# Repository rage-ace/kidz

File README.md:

# kidz

Find out more at [notes.skytect.one/robocup](https://notes.skytect.one/robocup)!

```bash
.
├── designs/               # All CAD designs are located here
│   └── pcb-schematics/        # PCB schematics
│       ├── layer1/                # Layer 1 PCB
│       ├── layer2/                # Layer 2 PCB
│       ├── layer3/                # Layer 3 PCB
│       └── layer4/                # Layer 4 PCB
├── software/              # All code is located here
│   ├── coral/             # Code for the Coral Dev Board Mini
│   │   └── ...
│   └── microcontrollers/  # Code for the Teensy 4.0 and STM32F103CBT6s
│       ├── include/           # Shared header files
│       ├── lib/               # Shared libraries
│       ├── src/
│       │   ├── stm32_mux/         # Code for the Layer 1 STM32
│       │   │   ├── include/           # Header files
│       │   │   ├── lib/               # Libraries
│       │   │   ├── main.cpp           # Source code
│       │   │   └── ...
│       │   ├── stm32_imu/         # Code for the Layer 4 IMU STM32
│       │   │   ├── include/           # Header files
│       │   │   ├── lib/               # Libraries
│       │   │   ├── main.cpp           # Source code
│       │   │   └── ...
│       │   ├── stm32_tof/        # Code for the Layer 4 TOF STM32
│       │   │   ├── include/           # Header files
│       │   │   ├── lib/               # Libraries
│       │   │   ├── main.cpp           # Source code
│       │   │   └── ...
│       │   ├── teensy/            # Code for the Layer 3 Teensy
│       │   │   ├── include/           # Header files
│       │   │   ├── lib/               # Libraries
│       │   │   ├── main.cpp           # Source code
│       │   │   └── ...
│       │   └── ...            # Shared source code
│       ├── platform.ini       # PlatformIO configuration file
│       └── ...
├── .gitignore
├── LICENSE
└── README.md
```

## Coral

[Click Me!](software/coral)

## Microcontrollers

### Execution

```bash
cd software/microcontrollers
# Upload and run to Teensy
pio run -e teensy -t upload -t monitor
# Upload to Layer 1 STM32
pio run -e stm32_mux -t upload
```

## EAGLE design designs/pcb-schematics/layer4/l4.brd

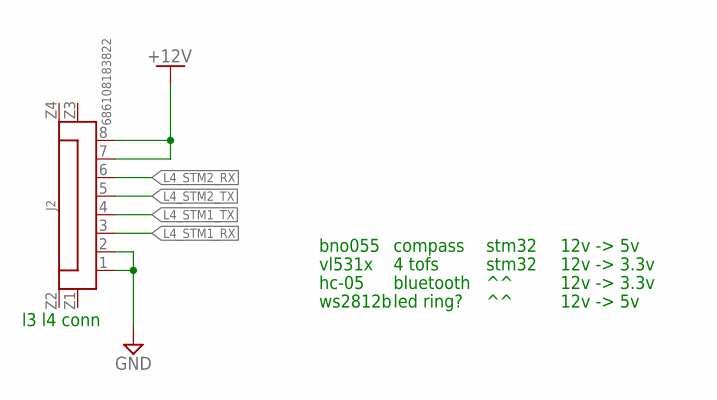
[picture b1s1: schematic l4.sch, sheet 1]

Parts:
J2: 686108183822

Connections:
+12V: J2.7, J2.8; also elsewhere on the board
GND: J2.1, J2.2; also elsewhere on the board
L4_STM1_RX: J2.3; also elsewhere on the board
L4_STM1_TX: J2.4; also elsewhere on the board
L4_STM2_RX: J2.6; also elsewhere on the board
L4_STM2_TX: J2.5; also elsewhere on the board

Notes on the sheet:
compass
stm32
4 tofs
bluetooth
led ring?
bno055
ws2812b
vl531x
hc-05
12v -> 5v
12v -> 3.3v
l3 l4 conn

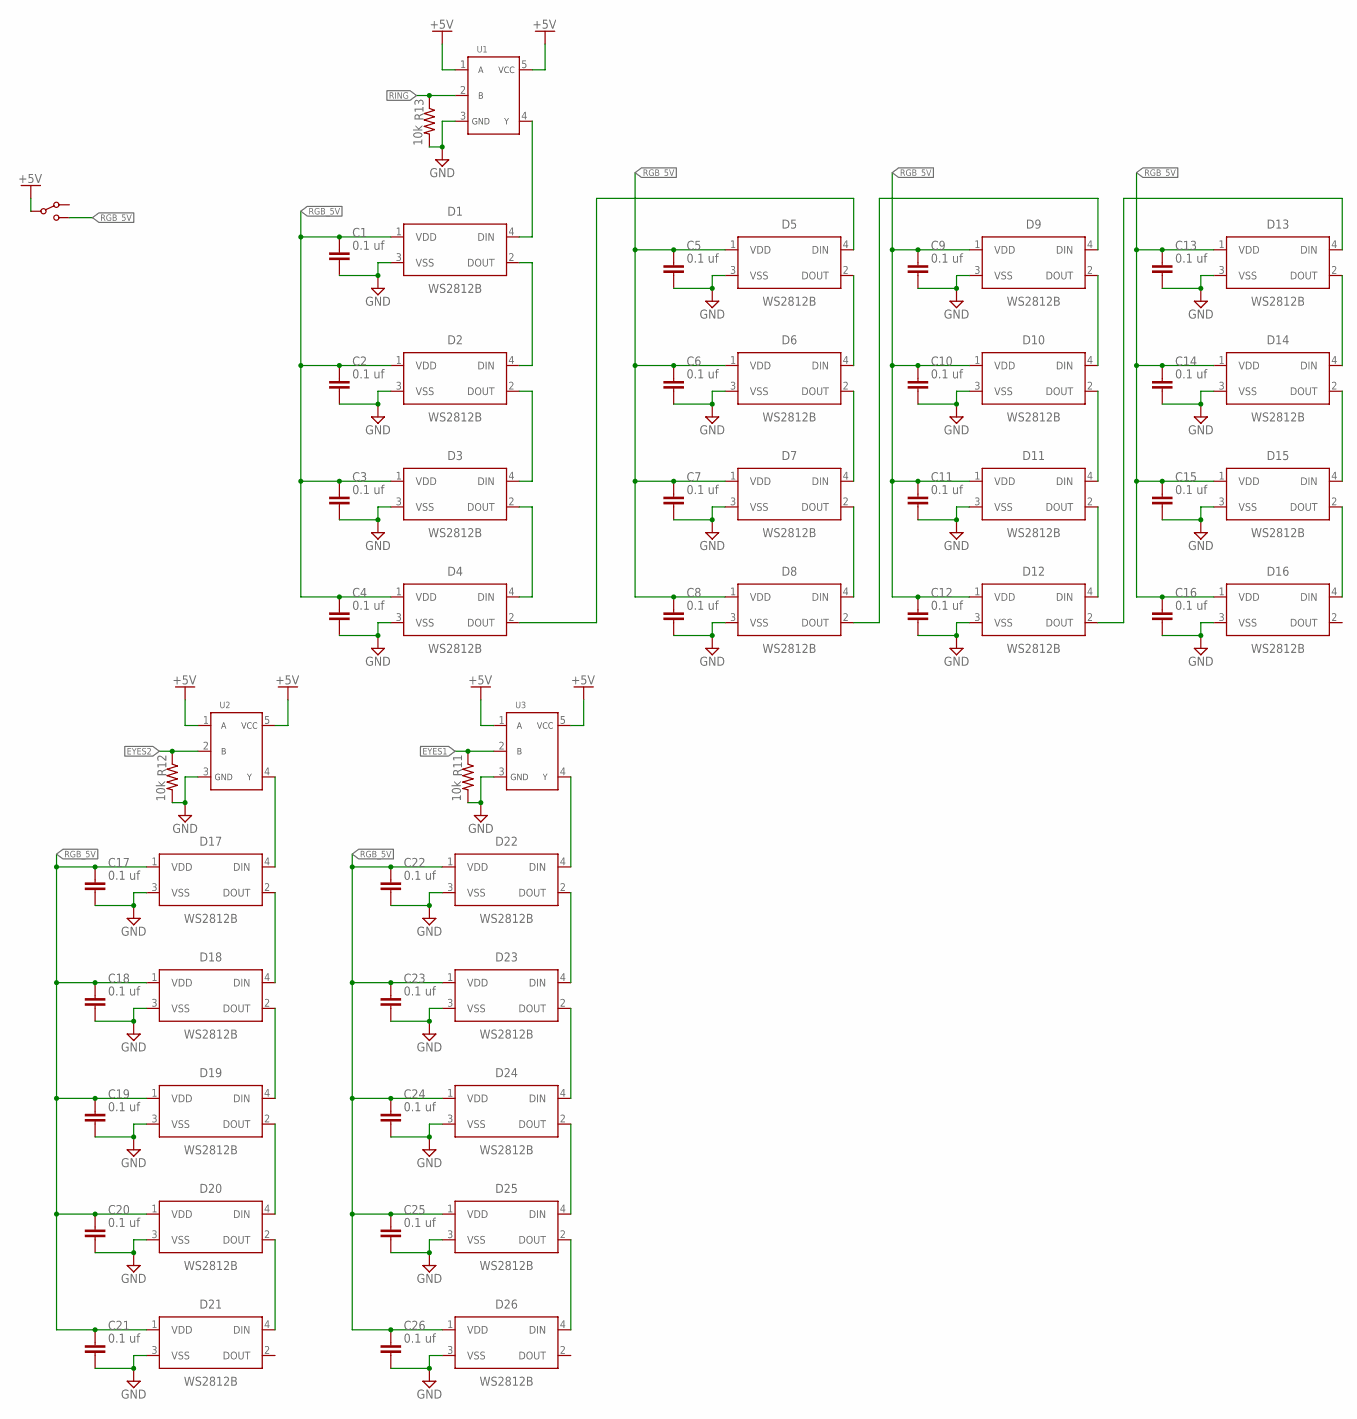
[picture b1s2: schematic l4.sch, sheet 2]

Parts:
C1, C2, C3, C4, C5, C6, C7, C8, C9, C10, C11, C12, C13, C14, C15, C16, C17, C18, C19, C20, C21, C22, C23, C24, C25, C26: 0.1 uf; CAPC1608X85
D1, D2, D3, D4, D5, D6, D7, D8, D9, D10, D11, D12, D13, D14, D15, D16, D17, D18, D19, D20, D21, D22, D23, D24, D25, D26: WS2812B
R11, R12, R13: 10k; RESC1608X60
S1: SPDT-SLIDE-SWITCHSWITCH-TH; SWITCH-TH
U1, U2, U3: SN74AHCT1G08; SOT23-5

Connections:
+5V: S1.P$2, U1.1, U1.5, U2.1, U2.5, U3.1, U3.5; also elsewhere on the board
EYES1: R11.1, U3.2; also elsewhere on the board
EYES2: R12.1, U2.2; also elsewhere on the board
GND: C1.2, C2.2, C3.2, C4.2, C5.2, C6.2, C7.2, C8.2, C9.2, C10.2, C11.2, C12.2, C13.2, C14.2, C15.2, C16.2, C17.2, C18.2, C19.2, C20.2, C21.2, C22.2, C23.2, C24.2, C25.2, C26.2, D1.3 (VSS), D2.3 (VSS), D3.3 (VSS), D4.3 (VSS), D5.3 (VSS), D6.3 (VSS), D7.3 (VSS), D8.3 (VSS), D9.3 (VSS), D10.3 (VSS), D11.3 (VSS), D12.3 (VSS), D13.3 (VSS), D14.3 (VSS), D15.3 (VSS), D16.3 (VSS), D17.3 (VSS), D18.3 (VSS), D19.3 (VSS), D20.3 (VSS), D21.3 (VSS), D22.3 (VSS), D23.3 (VSS), D24.3 (VSS), D25.3 (VSS), D26.3 (VSS), R11.2, R12.2, R13.2, U1.3, U2.3, U3.3; also elsewhere on the board
unnamed: D1.2 (DOUT), D2.4 (DIN)
unnamed: D2.2 (DOUT), D3.4 (DIN)
unnamed: D3.2 (DOUT), D4.4 (DIN)
unnamed: D9.2 (DOUT), D10.4 (DIN)
unnamed: D10.2 (DOUT), D11.4 (DIN)
unnamed: D1.4 (DIN), U1.4
unnamed: D11.2 (DOUT), D12.4 (DIN)
unnamed: D15.2 (DOUT), D16.4 (DIN)
unnamed: D14.2 (DOUT), D15.4 (DIN)
unnamed: D13.2 (DOUT), D14.4 (DIN)
unnamed: D5.2 (DOUT), D6.4 (DIN)
unnamed: D6.2 (DOUT), D7.4 (DIN)
unnamed: D7.2 (DOUT), D8.4 (DIN)
unnamed: D8.2 (DOUT), D9.4 (DIN)
unnamed: D12.2 (DOUT), D13.4 (DIN)
unnamed: D4.2 (DOUT), D5.4 (DIN)
unnamed: D20.2 (DOUT), D21.4 (DIN)
unnamed: D19.2 (DOUT), D20.4 (DIN)
unnamed: D18.2 (DOUT), D19.4 (DIN)
unnamed: D17.2 (DOUT), D18.4 (DIN)
unnamed: D22.2 (DOUT), D23.4 (DIN)
unnamed: D23.2 (DOUT), D24.4 (DIN)
unnamed: D24.2 (DOUT), D25.4 (DIN)
unnamed: D25.2 (DOUT), D26.4 (DIN)
unnamed: D22.4 (DIN), U3.4
unnamed: D17.4 (DIN), U2.4
RGB_5V: C1.1, C2.1, C3.1, C4.1, C5.1, C6.1, C7.1, C8.1, C9.1, C10.1, C11.1, C12.1, C13.1, C14.1, C15.1, C16.1, C17.1, C18.1, C19.1, C20.1, C21.1, C22.1, C23.1, C24.1, C25.1, C26.1, D1.1 (VDD), D2.1 (VDD), D3.1 (VDD), D4.1 (VDD), D5.1 (VDD), D6.1 (VDD), D7.1 (VDD), D8.1 (VDD), D9.1 (VDD), D10.1 (VDD), D11.1 (VDD), D12.1 (VDD), D13.1 (VDD), D14.1 (VDD), D15.1 (VDD), D16.1 (VDD), D17.1 (VDD), D18.1 (VDD), D19.1 (VDD), D20.1 (VDD), D21.1 (VDD), D22.1 (VDD), D23.1 (VDD), D24.1 (VDD), D25.1 (VDD), D26.1 (VDD), S1.P$3
RING: R13.1, U1.2; also elsewhere on the board

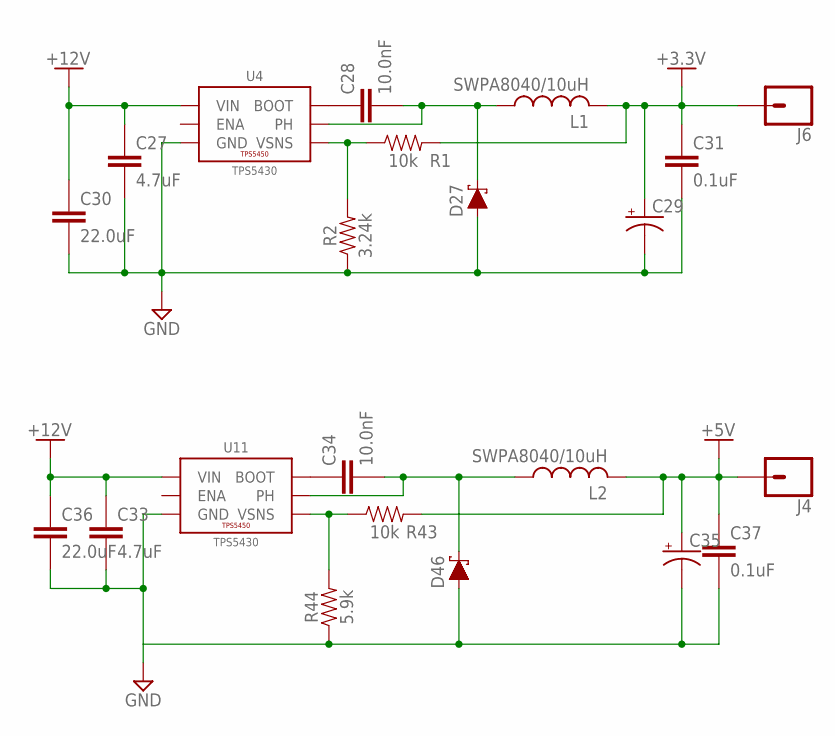
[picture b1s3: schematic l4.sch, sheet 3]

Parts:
C27, C33: 4.7uF; C0603
C28, C34: 10.0nF; C0603
C29, C35: 220uF; D/7343-31R
C30, C36: 22.0uF; C1210
C31, C37: 0.1uF; C0603
D27, D46: 3A/40V/500mV; SMA-DIODE
J4, J6: CONN_01; 1X01
L1, L2: SWPA8040/10uH; SWPA8040
R1, R43: 10k; R0603
R2: 3.24k; R0603
R44: 5.9k; R0603
U4, U11: TPS5430; POWERPAD-SOIC-8

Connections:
+3.3V: C29.+, C31.1, J6.1, L1.P2 (2), R1.2; also elsewhere on the board
+5V: C35.+, C37.1, J4.1, L2.P2 (2), R43.2; also elsewhere on the board
+12V: C27.1, C30.1, C33.1, C36.1, U4.7 (VIN), U11.7 (VIN); also elsewhere on the board
GND: C27.2, C29.-, C30.2, C31.2, C33.2, C35.-, C36.2, C37.2, D27.A, D46.A, R2.1, R44.1, U4.6 (GND), U4.9 (GND), U4.P$1 (GND), U4.P$2 (GND), U4.P$3 (GND), U4.P$4 (GND), U4.P$5 (GND), U4.P$6 (GND), U11.6 (GND), U11.9 (GND), U11.P$1 (GND), U11.P$2 (GND), U11.P$3 (GND), U11.P$4 (GND), U11.P$5 (GND), U11.P$6 (GND); also elsewhere on the board
unnamed: C28.2, D27.C, L1.P1 (1), U4.8 (PH)
unnamed: R1.1, R2.2, U4.4 (VSNS)
unnamed: C28.1, U4.1 (BOOT)
unnamed: C34.2, D46.C, L2.P1 (1), U11.8 (PH)
unnamed: R43.1, R44.2, U11.4 (VSNS)
unnamed: C34.1, U11.1 (BOOT)

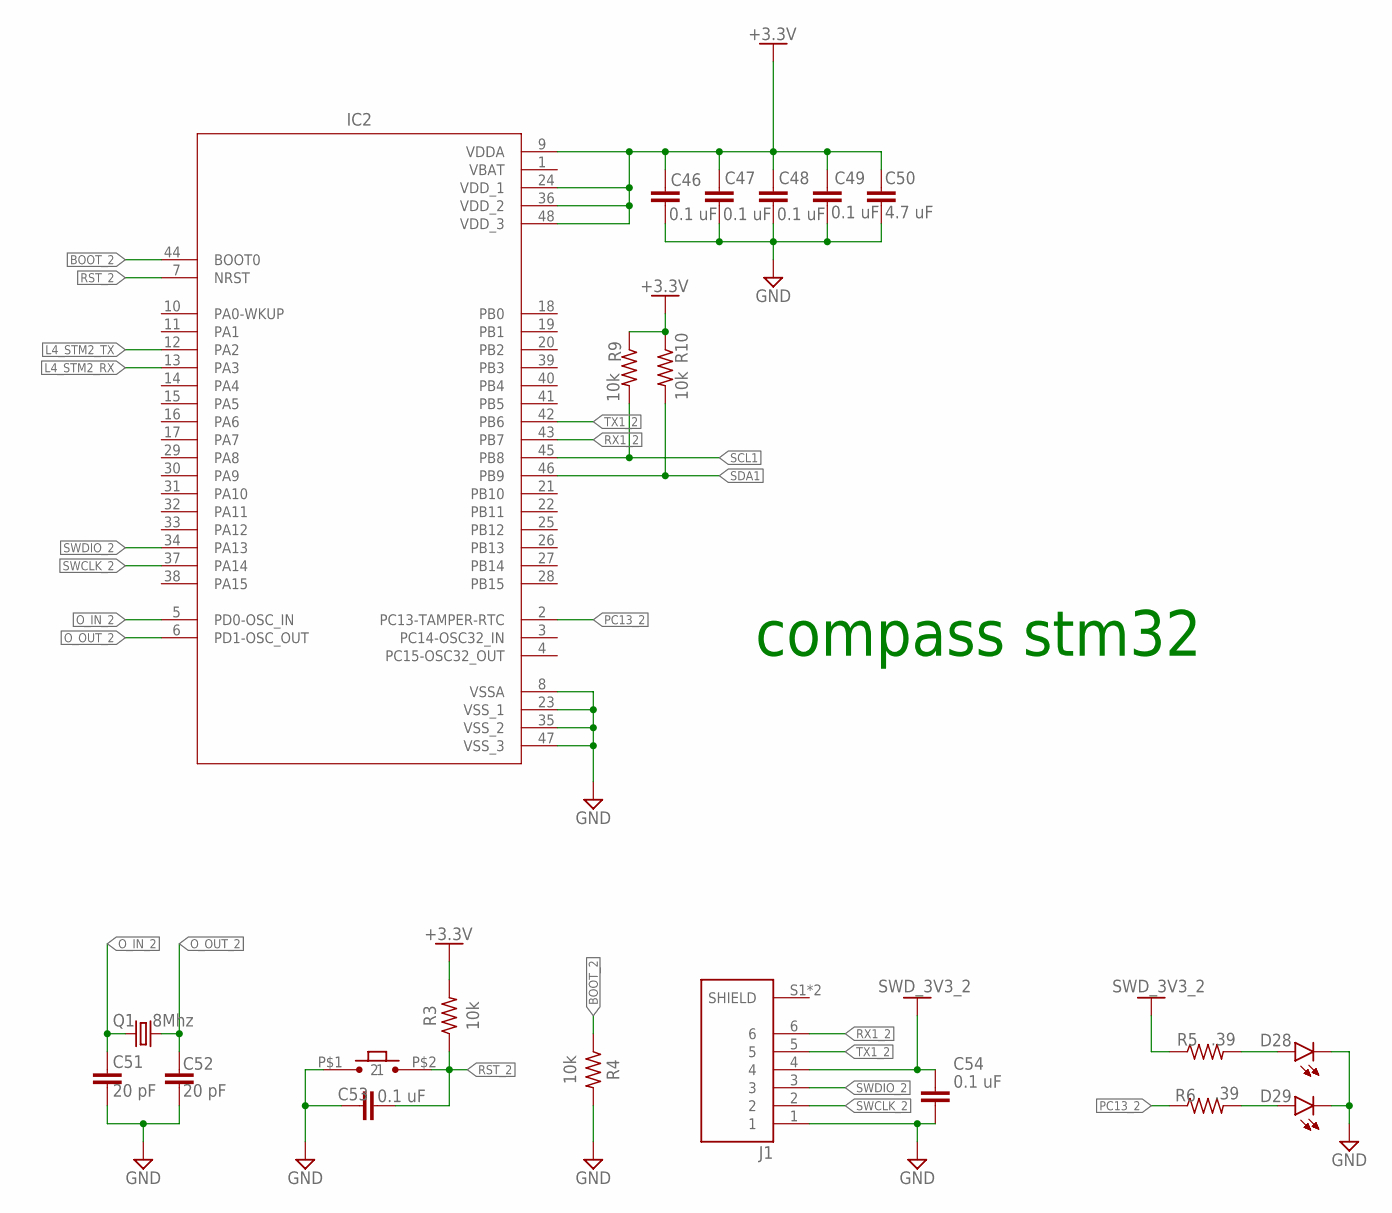
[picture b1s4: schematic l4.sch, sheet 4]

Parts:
C46, C47, C48, C49, C53, C54: 0.1 uF; CAPC1608X85
C50: 4.7 uF; CAPC1608X85
C51, C52: 20 pF; CAPC1608X85
D28, D29: CHIP-FLAT-G_0603-0.35MM; LEDC1608X35N_FLAT-G
IC2: STM32F103_QFP; QFP50P900X900X160-48N
J1: SM06B-SRSS-TB(LF)(SN); JST_SM06B-SRSS-TB(LF)(SN)
Q1: 8Mhz; CTS406
R3, R4, R9, R10: 10k; RESC1608X60
R5, R6: .39; RESC1608X60
U$2: SMOL_TACTILE_3X4MM

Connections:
+3.3V: C46.1, C47.1, C48.1, C49.1, C50.1, IC2.9 (VDDA), IC2.24 (VDD_1), IC2.36 (VDD_2), IC2.48 (VDD_3), R3.2, R9.1, R10.1; also elsewhere on the board
BOOT_2: IC2.44 (BOOT0), R4.1
GND: C46.2, C47.2, C48.2, C49.2, C50.2, C51.2, C52.2, C53.1, C54.2, D28.C, D29.C, IC2.8 (VSSA), IC2.23 (VSS_1), IC2.35 (VSS_2), IC2.47 (VSS_3), J1.1, R4.2, U$2.P$1 (1); also elsewhere on the board
L4_STM2_RX: IC2.13 (PA3); also elsewhere on the board
L4_STM2_TX: IC2.12 (PA2); also elsewhere on the board
unnamed: D28.A, R5.2
unnamed: D29.A, R6.2
O_IN_2: C51.1, IC2.5 (PD0-OSC_IN), Q1.1
O_OUT_2: C52.1, IC2.6 (PD1-OSC_OUT), Q1.3 (2)
PC13_2: IC2.2 (PC13-TAMPER-RTC), R6.1
RST_2: C53.2, IC2.7 (NRST), R3.1, U$2.P$2 (2)
RX1_2: IC2.43 (PB7), J1.6
SCL1: IC2.45 (PB8), R9.2; also elsewhere on the board
SDA1: IC2.46 (PB9), R10.2; also elsewhere on the board
SWCLK_2: IC2.37 (PA14), J1.2
SWDIO_2: IC2.34 (PA13), J1.3
SWD_3V3_2: C54.1, J1.4, R5.1
TX1_2: IC2.42 (PB6), J1.5
VBAT: IC2.1 (VBAT); also elsewhere on the board

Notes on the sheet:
compass stm32

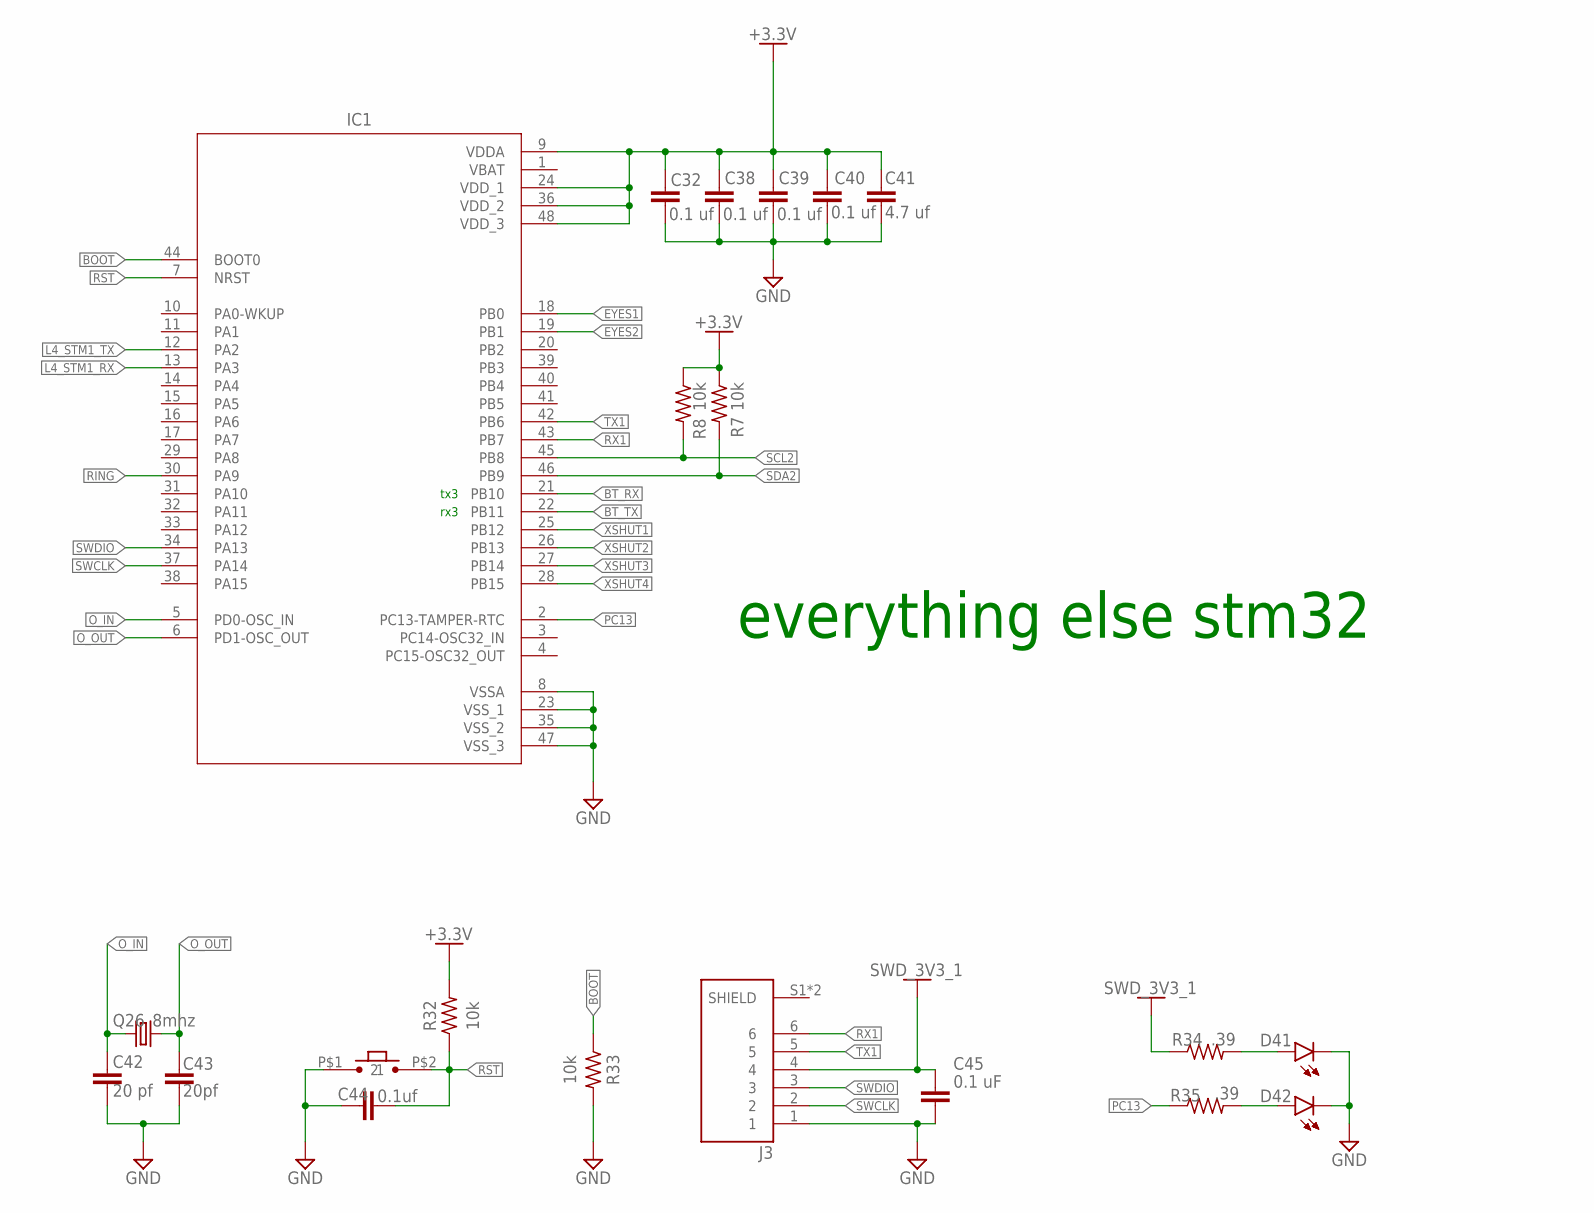
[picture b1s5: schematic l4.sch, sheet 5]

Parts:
C32, C38, C39, C40: 0.1 uf; CAPC1608X85
C41: 4.7 uf; CAPC1608X85
C42: 20 pf; CAPC1608X85
C43: 20pf; CAPC1608X85
C44: 0.1uf; CAPC1608X85
C45: 0.1 uF; CAPC1608X85
D41, D42: CHIP-FLAT-G_0603-0.35MM; LEDC1608X35N_FLAT-G
IC1: STM32F103_QFP; QFP50P900X900X160-48N
J3: SM06B-SRSS-TB(LF)(SN); JST_SM06B-SRSS-TB(LF)(SN)
Q26: 8mhz; CTS406
R7, R8, R32, R33: 10k; RESC1608X60
R34, R35: .39; RESC1608X60
U$1: SMOL_TACTILE_3X4MM

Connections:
+3.3V: C32.1, C38.1, C39.1, C40.1, C41.1, IC1.9 (VDDA), IC1.24 (VDD_1), IC1.36 (VDD_2), IC1.48 (VDD_3), R7.1, R8.1, R32.2; also elsewhere on the board
BOOT: IC1.44 (BOOT0), R33.1
BT_RX: IC1.21 (PB10); also elsewhere on the board
BT_TX: IC1.22 (PB11); also elsewhere on the board
EYES1: IC1.18 (PB0); also elsewhere on the board
EYES2: IC1.19 (PB1); also elsewhere on the board
GND: C32.2, C38.2, C39.2, C40.2, C41.2, C42.2, C43.2, C44.1, C45.2, D41.C, D42.C, IC1.8 (VSSA), IC1.23 (VSS_1), IC1.35 (VSS_2), IC1.47 (VSS_3), J3.1, R33.2, U$1.P$1 (1); also elsewhere on the board
L4_STM1_RX: IC1.13 (PA3); also elsewhere on the board
L4_STM1_TX: IC1.12 (PA2); also elsewhere on the board
unnamed: D41.A, R34.2
unnamed: D42.A, R35.2
O_IN: C42.1, IC1.5 (PD0-OSC_IN), Q26.1
O_OUT: C43.1, IC1.6 (PD1-OSC_OUT), Q26.3 (2)
PC13: IC1.2 (PC13-TAMPER-RTC), R35.1
RING: IC1.30 (PA9); also elsewhere on the board
RST: C44.2, IC1.7 (NRST), R32.1, U$1.P$2 (2)
RX1: IC1.43 (PB7), J3.6
SCL2: IC1.45 (PB8), R8.2; also elsewhere on the board
SDA2: IC1.46 (PB9), R7.2; also elsewhere on the board
SWCLK: IC1.37 (PA14), J3.2
SWDIO: IC1.34 (PA13), J3.3
SWD_3V3_1: C45.1, J3.4, R34.1
TX1: IC1.42 (PB6), J3.5
VBAT: IC1.1 (VBAT); also elsewhere on the board
XSHUT1: IC1.25 (PB12); also elsewhere on the board
XSHUT2: IC1.26 (PB13); also elsewhere on the board
XSHUT3: IC1.27 (PB14); also elsewhere on the board
XSHUT4: IC1.28 (PB15); also elsewhere on the board

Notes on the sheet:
everything else stm32
tx3
rx3

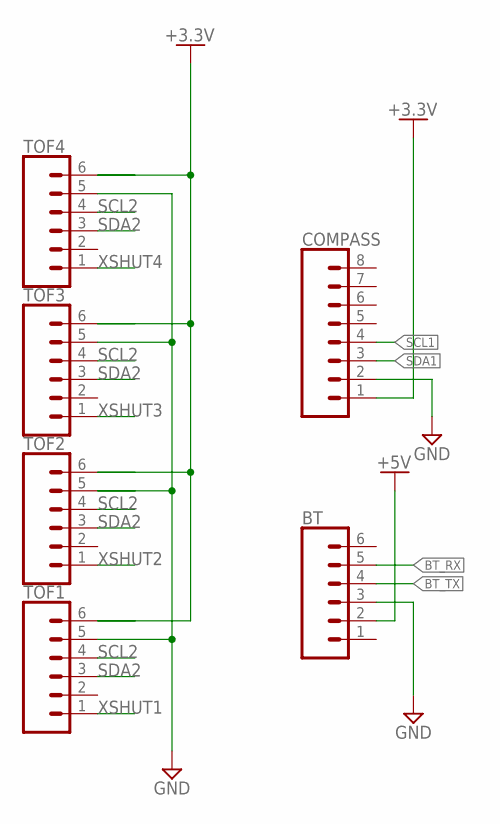
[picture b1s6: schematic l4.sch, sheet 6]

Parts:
BT: CONN_06LOCK; 1X06_LOCK
COMPASS: CONN_08LOCK; 1X08_LOCK
TOF1, TOF2, TOF3, TOF4: CONN_06LOCK; 1X06_LOCK

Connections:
+3.3V: COMPASS.1, TOF1.6, TOF2.6, TOF3.6, TOF4.6; also elsewhere on the board
+5V: BT.2; also elsewhere on the board
BT_RX: BT.5; also elsewhere on the board
BT_TX: BT.4; also elsewhere on the board
GND: BT.3, COMPASS.2, TOF1.5, TOF2.5, TOF3.5, TOF4.5; also elsewhere on the board
SCL1: COMPASS.4; also elsewhere on the board
SCL2: TOF1.4, TOF2.4, TOF3.4, TOF4.4; also elsewhere on the board
SDA1: COMPASS.3; also elsewhere on the board
SDA2: TOF1.3, TOF2.3, TOF3.3, TOF4.3; also elsewhere on the board
XSHUT1: TOF1.1; also elsewhere on the board
XSHUT2: TOF2.1; also elsewhere on the board
XSHUT3: TOF3.1; also elsewhere on the board
XSHUT4: TOF4.1; also elsewhere on the board

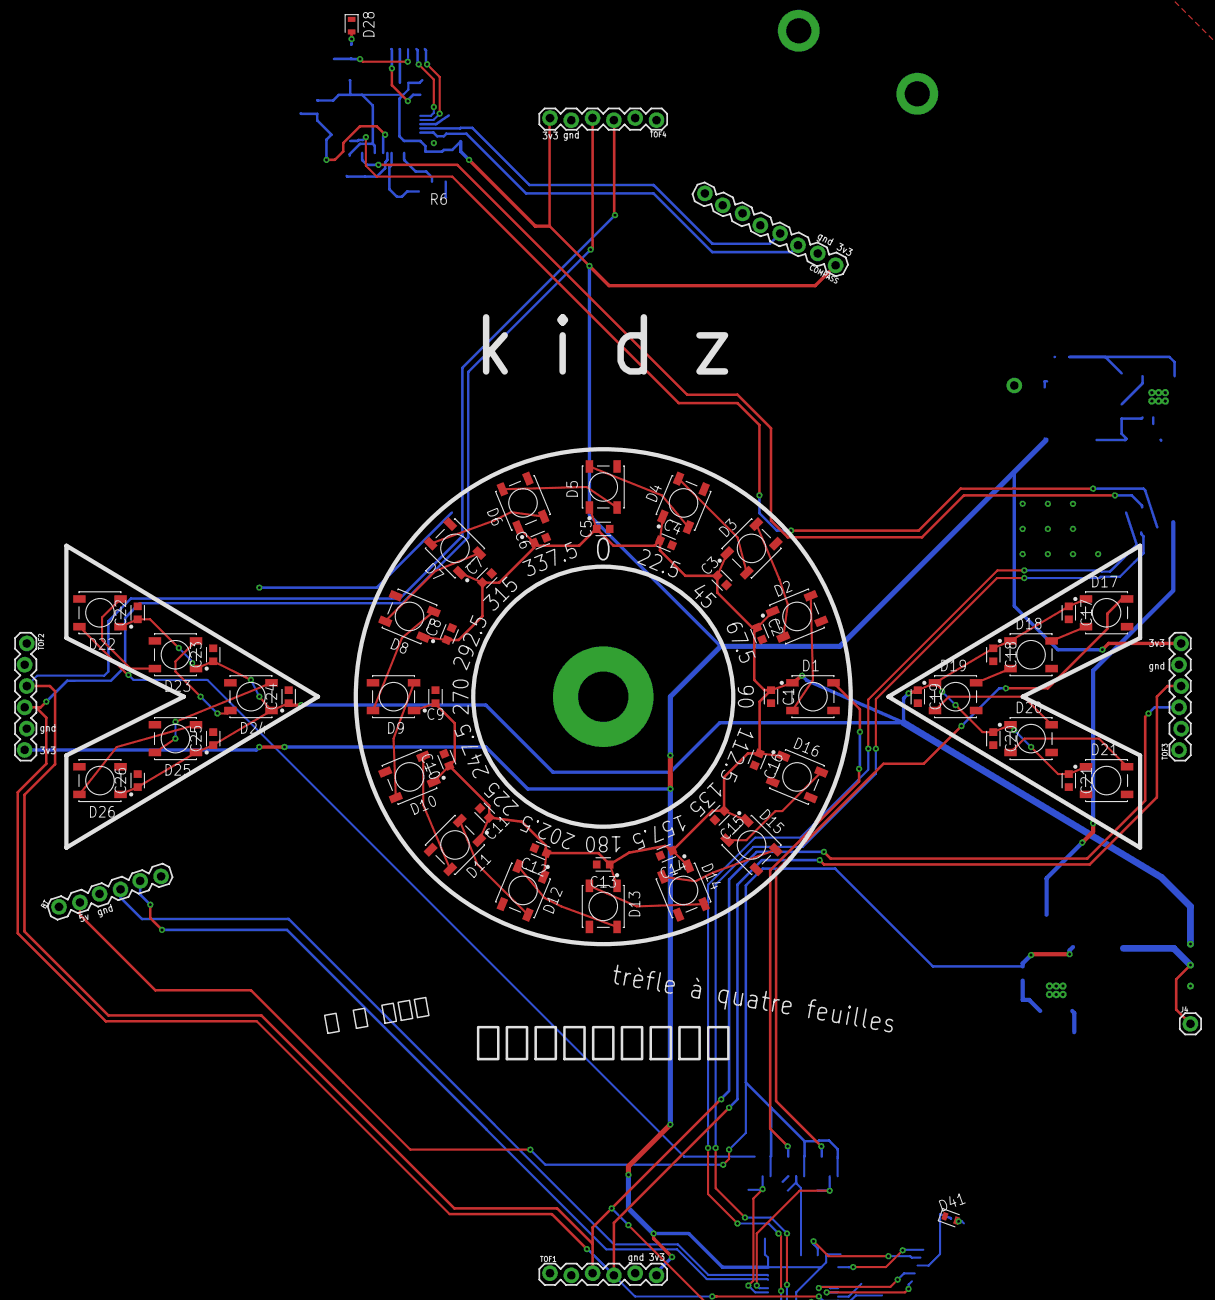
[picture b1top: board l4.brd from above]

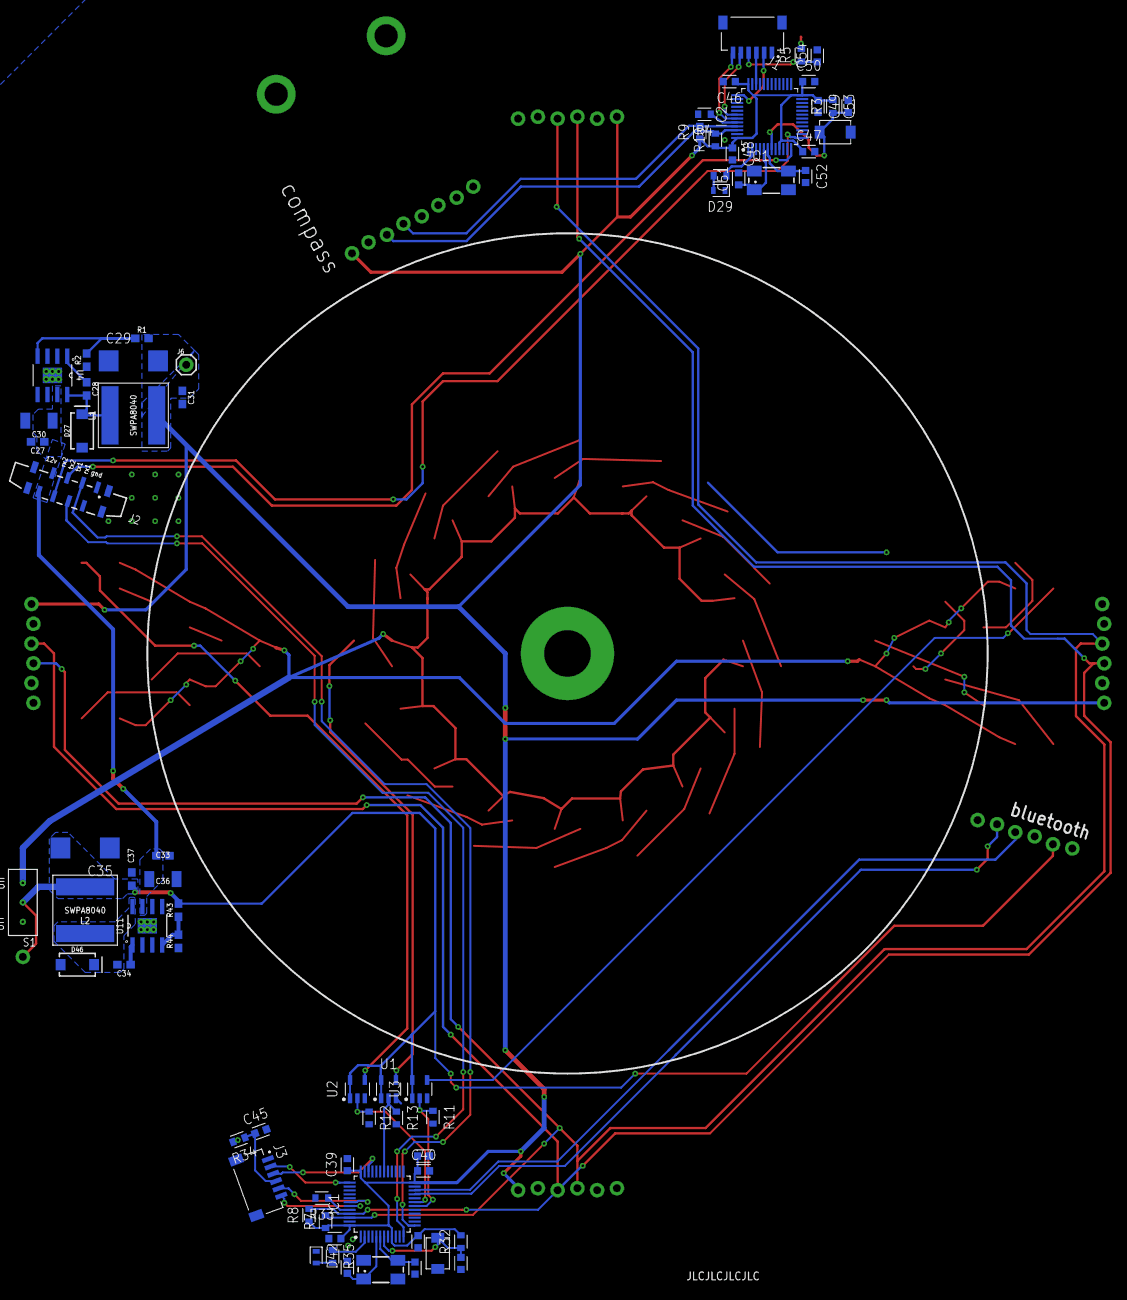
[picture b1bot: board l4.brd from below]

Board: 2 copper layers, 130 parts (69 on the bottom side), 79 nets.

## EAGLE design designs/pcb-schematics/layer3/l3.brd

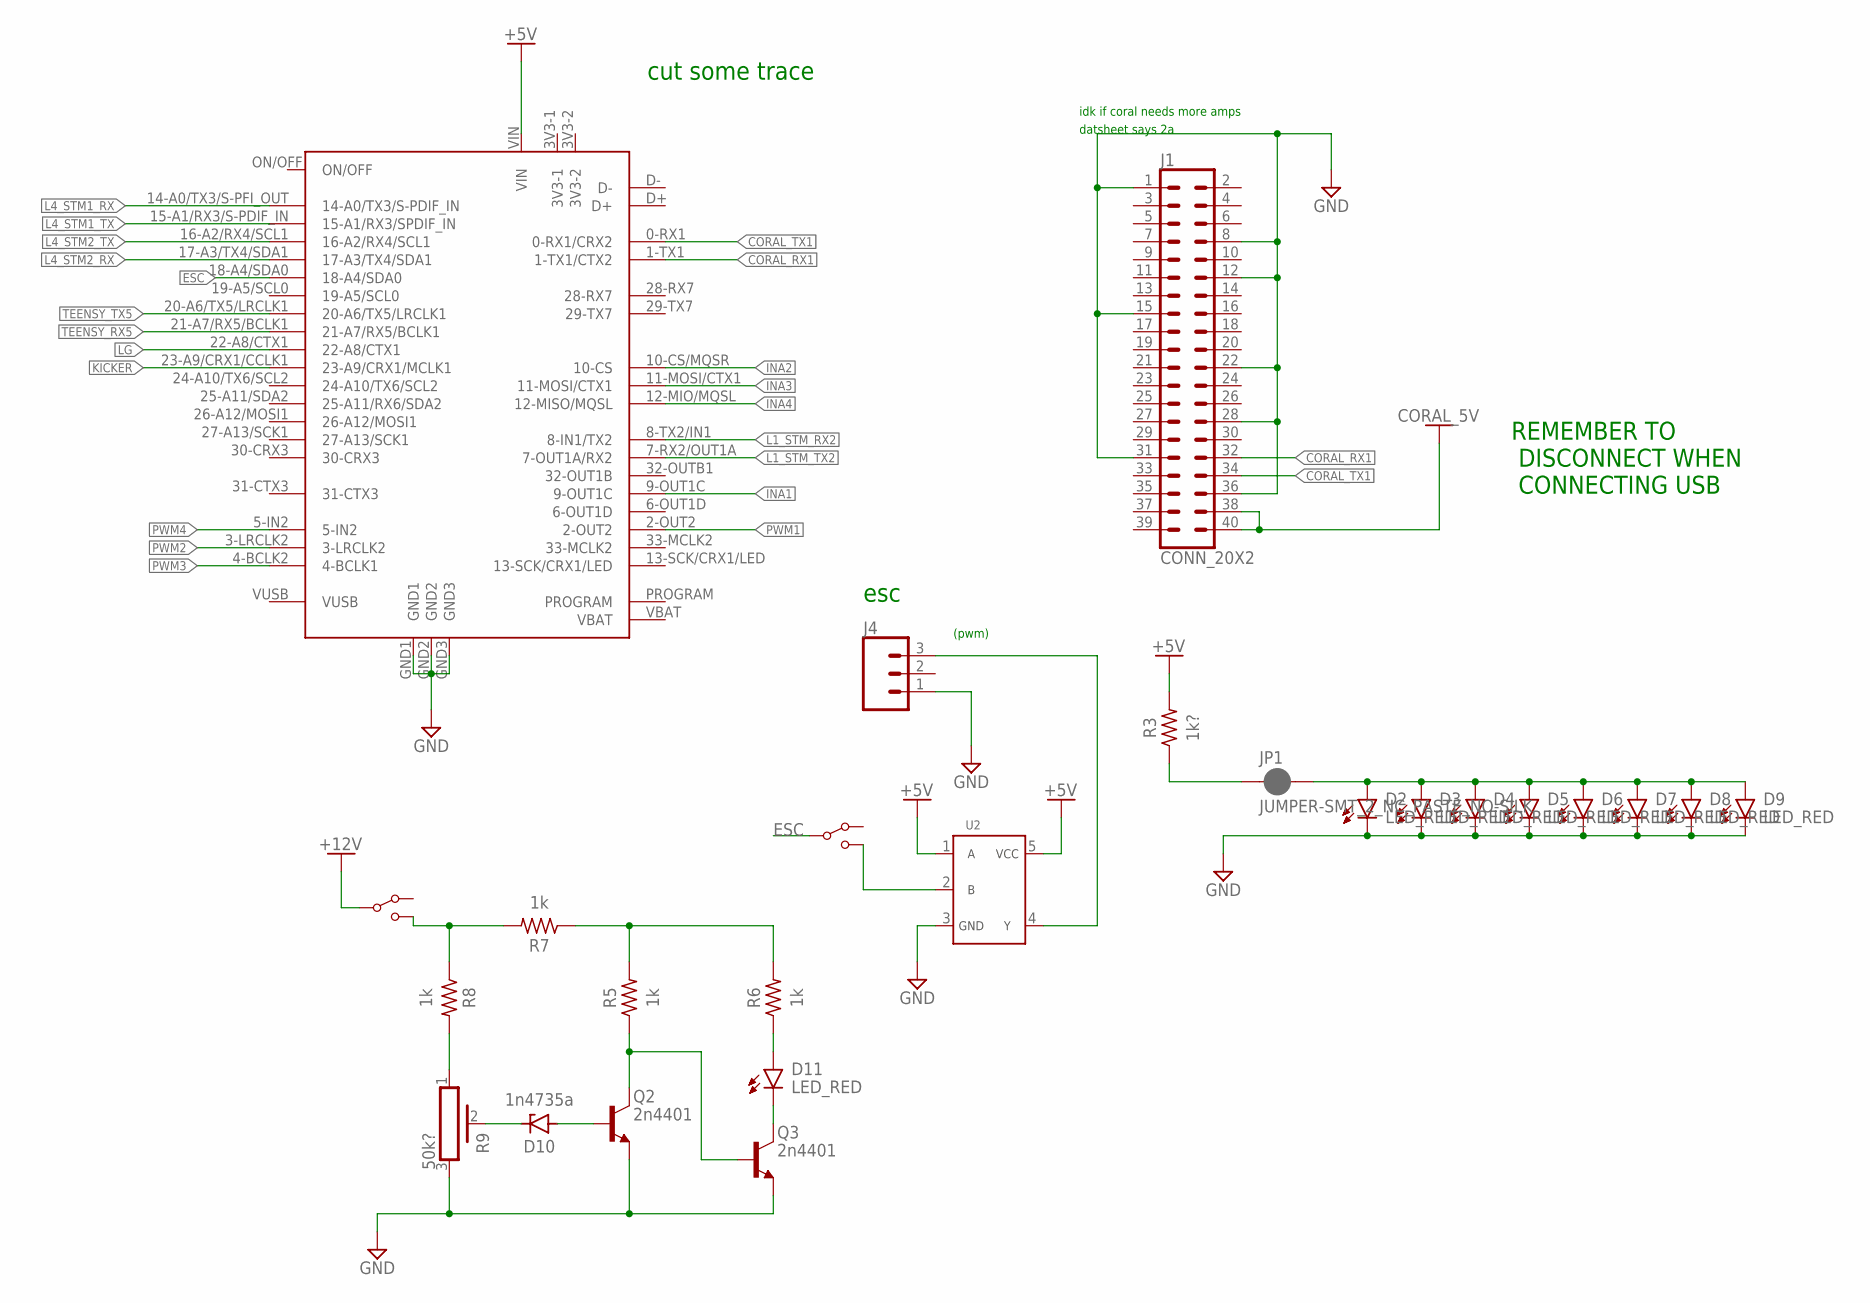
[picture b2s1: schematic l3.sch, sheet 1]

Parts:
D2, D3, D4, D5, D6, D7, D8, D9, D11: LED_RED; LEDC1608X55N_FLAT-R
D10: 1n4735a; DO41
J1: CONN_20X2; 2X20
J4: CONN_03LOCK; 1X03_LOCK
JP1: JUMPER-SMT_2_NC_PASTE_NO-SILK; SMT-JUMPER_2_NC_PASTE_NO-SILK
Q2, Q3: 2n4401; TO92
R3: 1k?; RESC1608X60
R5, R6, R7, R8: 1k; RESC1608X60
R9: 50k?; PV36X
S1, S2: SPDT-SLIDE-SWITCHSWITCH-TH; SWITCH-TH
U2: SN74AHCT1G08; SOT23-5
U$1: TEENSY40

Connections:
+5V: R3.2, U2.1, U2.5, U$1.VIN; also elsewhere on the board
+12V: S1.P$2; also elsewhere on the board
CORAL_5V: J1.38, J1.40; also elsewhere on the board
CORAL_RX1: J1.32, U$1.1-TX1 (1-TX1/CTX2)
CORAL_TX1: J1.34, U$1.0-RX1 (0-RX1/CRX2)
ESC: S2.P$2, U$1.18-A4/SDA0
GND: D2.C, D3.C, D4.C, D5.C, D6.C, D7.C, D8.C, D9.C, J1.1, J1.8, J1.12, J1.15, J1.22, J1.28, J1.31, J1.36, J4.1, Q2.1 (E), Q3.1 (E), R9.3, U2.3, U$1.GND1, U$1.GND2, U$1.GND3; also elsewhere on the board
INA1: U$1.9-OUT1C; also elsewhere on the board
INA2: U$1.10-CS/MQSR (10-CS); also elsewhere on the board
INA3: U$1.11-MOSI/CTX1; also elsewhere on the board
INA4: U$1.12-MIO/MQSL (12-MISO/MQSL); also elsewhere on the board
KICKER: U$1.23-A9/CRX1/CCLK1 (23-A9/CRX1/MCLK1); also elsewhere on the board
L1_STM_RX2: U$1.8-TX2/IN1 (8-IN1/TX2); also elsewhere on the board
L1_STM_TX2: U$1.7-RX2/OUT1A (7-OUT1A/RX2); also elsewhere on the board
L4_STM1_RX: U$1.14-A0/TX3/S-PFI_OUT (14-A0/TX3/S-PDIF_IN); also elsewhere on the board
L4_STM1_TX: U$1.15-A1/RX3/S-PDIF_IN (15-A1/RX3/SPDIF_IN); also elsewhere on the board
L4_STM2_RX: U$1.17-A3/TX4/SDA1; also elsewhere on the board
L4_STM2_TX: U$1.16-A2/RX4/SCL1; also elsewhere on the board
LG: U$1.22-A8/CTX1; also elsewhere on the board
unnamed: D2.A, D3.A, D4.A, D5.A, D6.A, D7.A, D8.A, D9.A, JP1.2
unnamed: JP1.1, R3.1
unnamed: D10.C, R9.2
unnamed: D10.A, Q2.2 (B)
unnamed: Q2.3 (C), Q3.2 (B), R5.1
unnamed: R8.2, R9.1
unnamed: R5.2, R6.2, R7.1
unnamed: D11.A, R6.1
unnamed: D11.C, Q3.3 (C)
unnamed: R7.2, R8.1, S1.P$3
unnamed: S2.P$3, U2.2
unnamed: J4.3, U2.4
PWM1: U$1.2-OUT2; also elsewhere on the board
PWM2: U$1.3-LRCLK2; also elsewhere on the board
PWM3: U$1.4-BCLK2 (4-BCLK1); also elsewhere on the board
PWM4: U$1.5-IN2; also elsewhere on the board
TEENSY_RX5: U$1.21-A7/RX5/BCLK1
TEENSY_TX5: U$1.20-A6/TX5/LRCLK1

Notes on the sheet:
idk if coral needs more amps
datsheet says 2a
REMEMBER TO DISCONNECT WHEN CONNECTING USB
cut some trace
esc
(pwm)

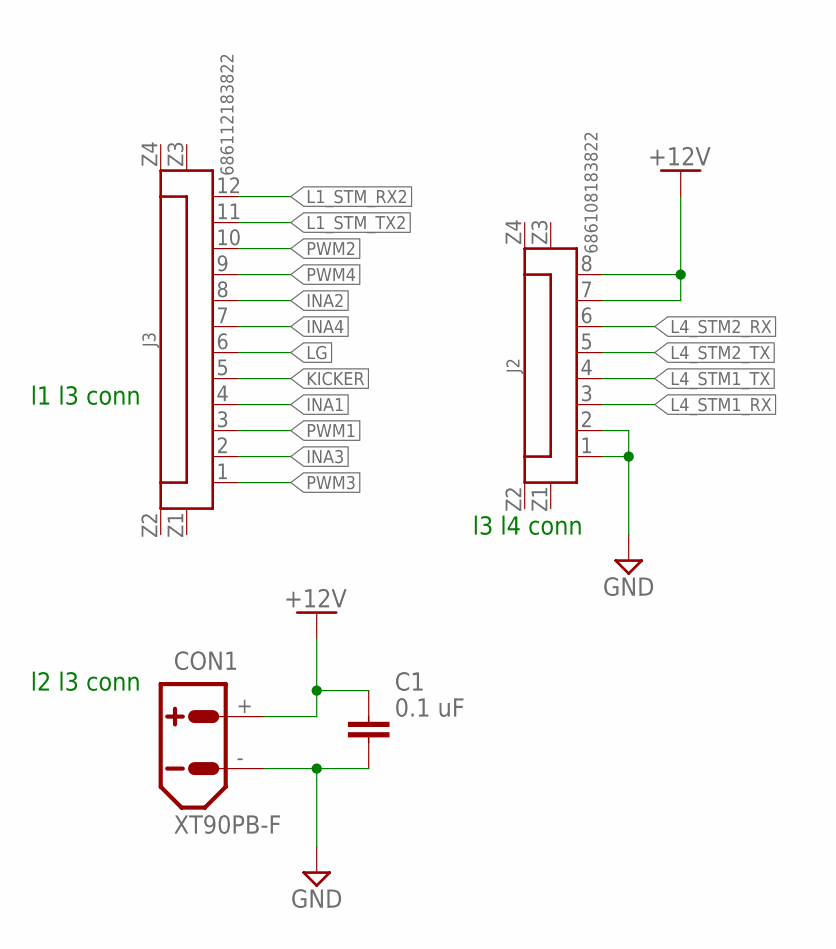
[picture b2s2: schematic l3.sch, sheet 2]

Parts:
C1: 0.1 uF; CAPC1608X85
CON1: XT90PB-F
J2: 686108183822
J3: 686112183822

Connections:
+12V: C1.1, CON1.+, J2.7, J2.8; also elsewhere on the board
GND: C1.2, CON1.-, J2.1, J2.2; also elsewhere on the board
INA1: J3.4; also elsewhere on the board
INA2: J3.8; also elsewhere on the board
INA3: J3.2; also elsewhere on the board
INA4: J3.7; also elsewhere on the board
KICKER: J3.5; also elsewhere on the board
L1_STM_RX2: J3.12; also elsewhere on the board
L1_STM_TX2: J3.11; also elsewhere on the board
L4_STM1_RX: J2.3; also elsewhere on the board
L4_STM1_TX: J2.4; also elsewhere on the board
L4_STM2_RX: J2.6; also elsewhere on the board
L4_STM2_TX: J2.5; also elsewhere on the board
LG: J3.6; also elsewhere on the board
PWM1: J3.3; also elsewhere on the board
PWM2: J3.10; also elsewhere on the board
PWM3: J3.1; also elsewhere on the board
PWM4: J3.9; also elsewhere on the board

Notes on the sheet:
l2 l3 conn
l1 l3 conn
l3 l4 conn

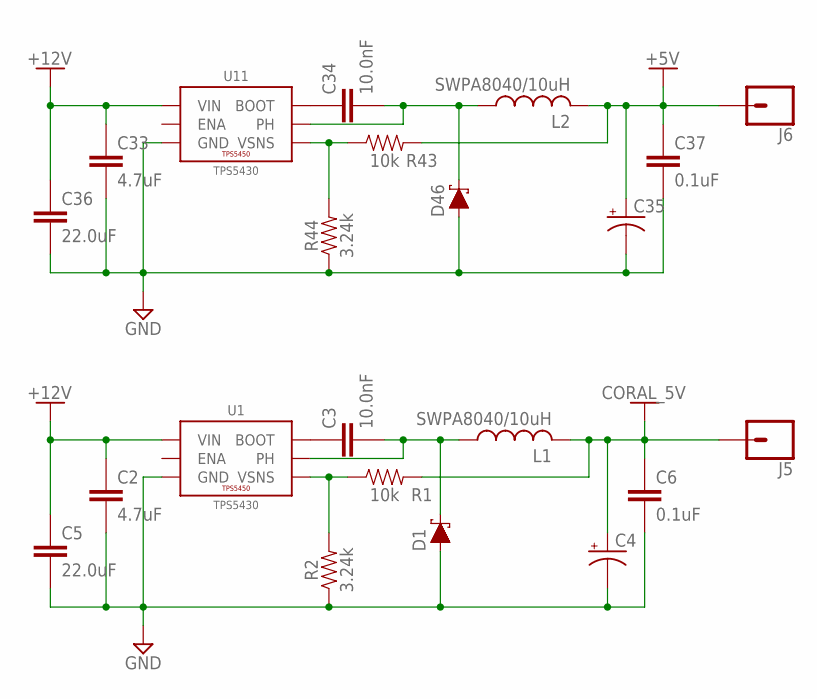
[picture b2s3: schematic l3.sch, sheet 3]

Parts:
C2, C33: 4.7uF; C0603
C3, C34: 10.0nF; C0603
C4, C35: 220uF; D/7343-31R
C5, C36: 22.0uF; C1210
C6, C37: 0.1uF; C0603
D1, D46: 3A/40V/500mV; SMA-DIODE
J5, J6: CONN_01; 1X01
L1, L2: SWPA8040/10uH; SWPA8040
R1, R43: 10k; R0603
R2, R44: 3.24k; R0603
U1, U11: TPS5430; POWERPAD-SOIC-8

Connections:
+5V: C35.+, C37.1, J6.1, L2.P2 (2), R43.2; also elsewhere on the board
+12V: C2.1, C5.1, C33.1, C36.1, U1.7 (VIN), U11.7 (VIN); also elsewhere on the board
CORAL_5V: C4.+, C6.1, J5.1, L1.P2 (2), R1.2; also elsewhere on the board
GND: C2.2, C4.-, C5.2, C6.2, C33.2, C35.-, C36.2, C37.2, D1.A, D46.A, R2.1, R44.1, U1.6 (GND), U1.9 (GND), U1.P$1 (GND), U1.P$2 (GND), U1.P$3 (GND), U1.P$4 (GND), U1.P$5 (GND), U1.P$6 (GND), U11.6 (GND), U11.9 (GND), U11.P$1 (GND), U11.P$2 (GND), U11.P$3 (GND), U11.P$4 (GND), U11.P$5 (GND), U11.P$6 (GND); also elsewhere on the board
unnamed: C3.2, D1.C, L1.P1 (1), U1.8 (PH)
unnamed: R1.1, R2.2, U1.4 (VSNS)
unnamed: C3.1, U1.1 (BOOT)
unnamed: C34.2, D46.C, L2.P1 (1), U11.8 (PH)
unnamed: R43.1, R44.2, U11.4 (VSNS)
unnamed: C34.1, U11.1 (BOOT)

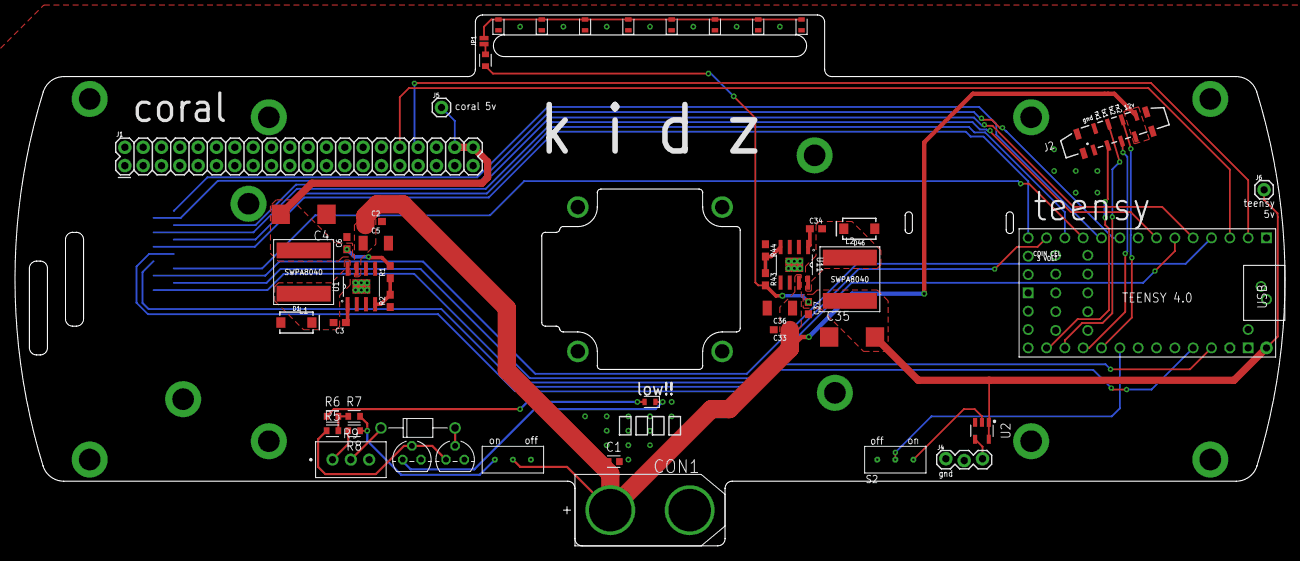
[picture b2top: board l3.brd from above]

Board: 2 copper layers, 176.0 x 73.6 mm, 51 parts (1 on the bottom side), 41 nets.

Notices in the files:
parts and their libraries:
SparkFun-Connectors: Licensing: Creative Commons ShareAlike 4.0 International - https://creativecommons.org/licenses/by-sa/4.0
Wurth_Power Magnetics_WE-PD: Copyright: Würth Elektronik
